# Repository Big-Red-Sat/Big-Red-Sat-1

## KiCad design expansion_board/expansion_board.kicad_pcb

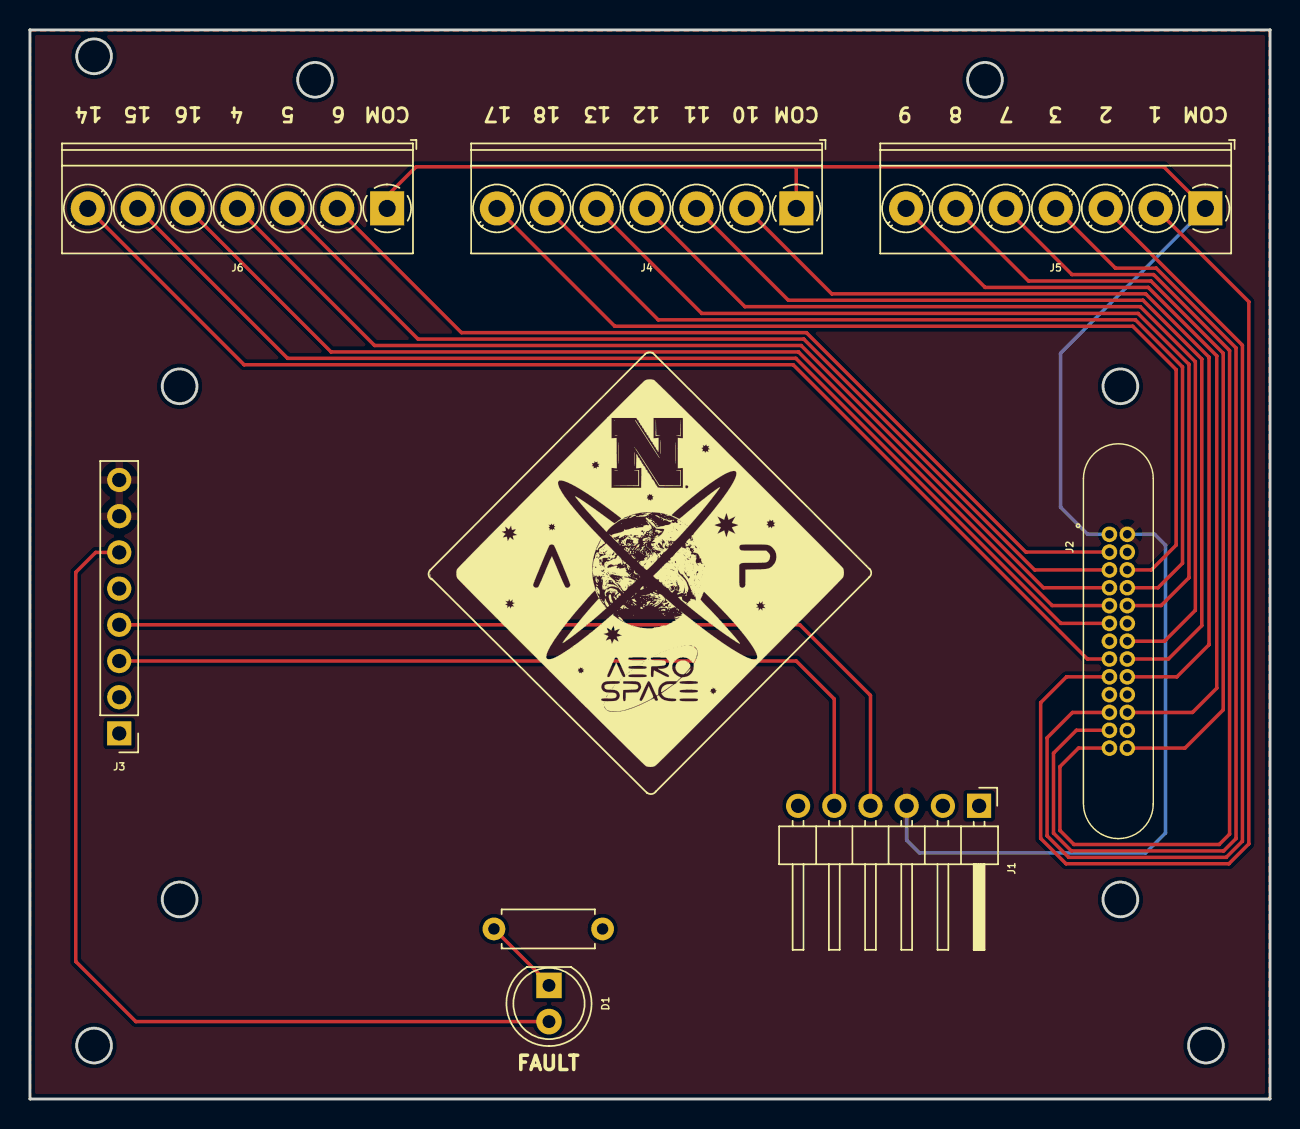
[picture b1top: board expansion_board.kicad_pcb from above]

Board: 2 copper layers, 87.0 x 75.0 mm, 8 parts (0 on the bottom side), 25 nets.

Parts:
D1: LED; LED_D5.0mm
FAULT: R; R_Axial_DIN0207_L6.3mm_D2.5mm_P7.62mm_Horizontal
J1: Conn_01x06_Female; PinHeader_1x06_P2.54mm_Horizontal
J2: G125-MH12605M4R; G125-MV12605M1P
J3: Conn_01x08_Female; PinHeader_1x08_P2.54mm_Vertical
J4, J5, J6: Screw_Terminal_01x07; TerminalBlock_Phoenix_PT-1,5-7-3.5-H_1x07_P3.50mm_Horizontal

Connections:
+3V3: J1.3, J2.14, J3.7, J3.8
GND: FAULT.2, J1.1, J2.19, J3.1, J3.2
unnamed: D1.1, FAULT.1
unnamed: D1.2, J3.6
unnamed: J1.4, J3.4
unnamed: J1.5, J3.3
unnamed: J2.1, J4.1, J5.1, J6.1
unnamed: J2.2, J6.2
unnamed: J2.3, J6.3
unnamed: J2.4, J6.4
unnamed: J2.5, J6.5
unnamed: J2.6, J6.6
unnamed: J2.8, J6.7
unnamed: J2.9, J5.2
unnamed: J2.11, J5.3
unnamed: J2.12, J5.4
unnamed: J2.13, J5.5
unnamed: J2.16, J4.7
unnamed: J2.17, J4.6
unnamed: J2.18, J4.5
unnamed: J2.20, J4.4
unnamed: J2.21, J4.3
unnamed: J2.22, J4.2
unnamed: J2.24, J5.7
unnamed: J2.26, J5.6

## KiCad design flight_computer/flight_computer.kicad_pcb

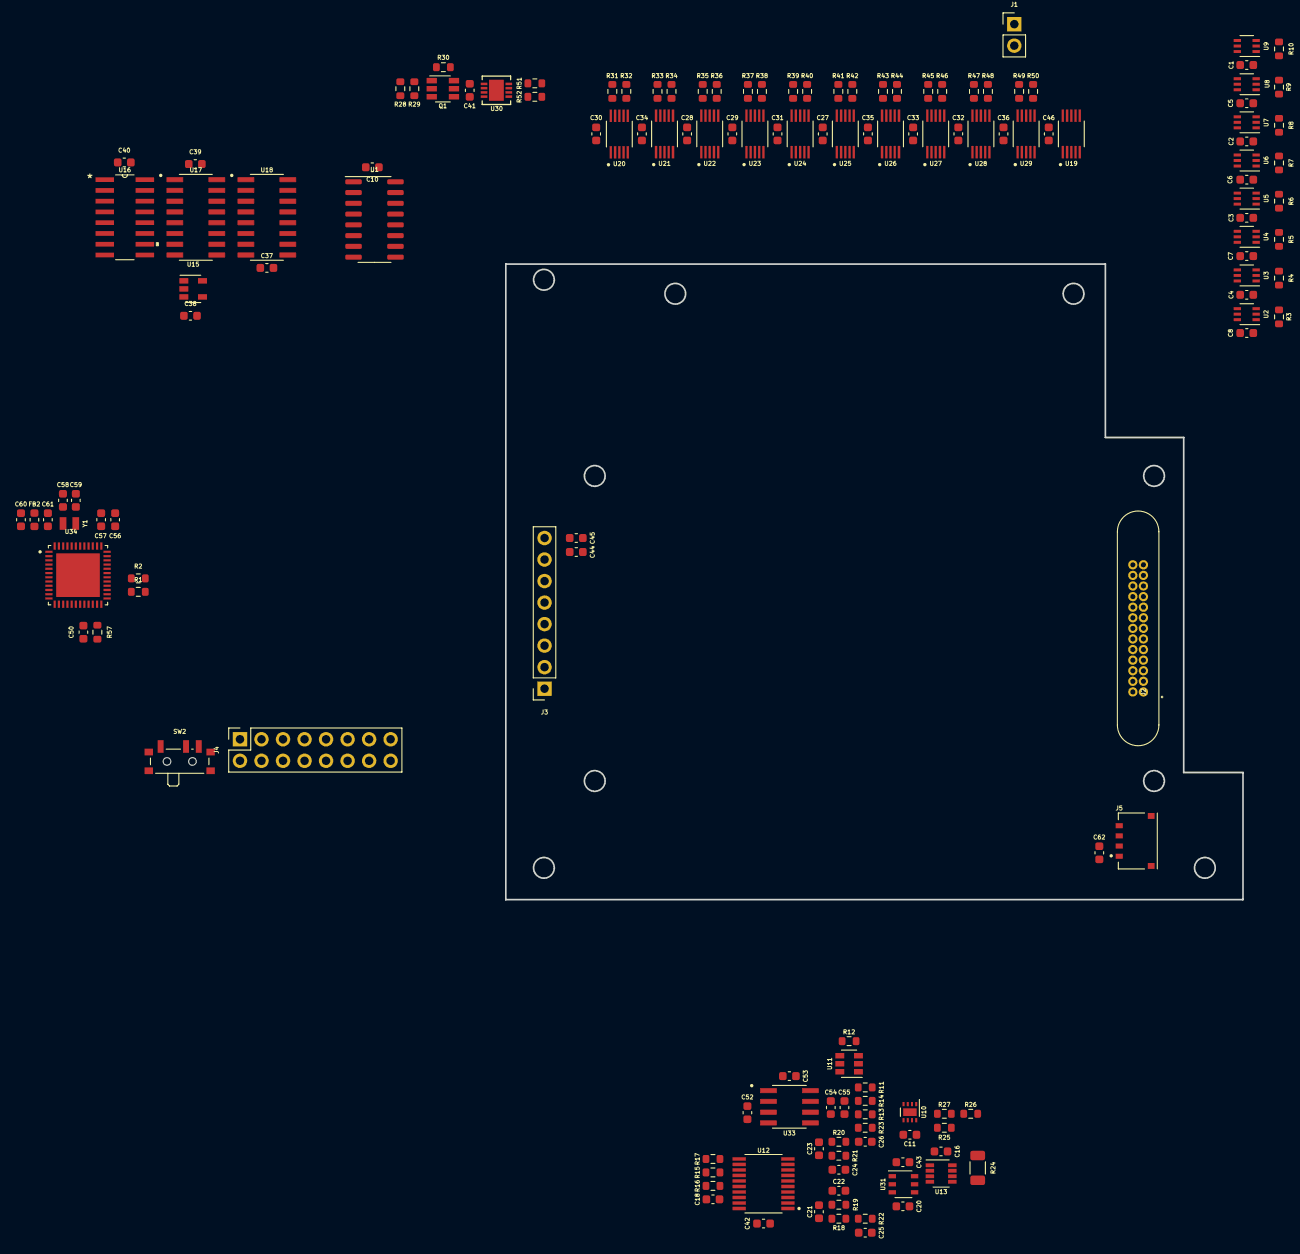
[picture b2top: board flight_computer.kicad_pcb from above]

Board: 4 copper layers, 145 parts (0 on the bottom side), 127 nets, no tracks yet.

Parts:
C1, C2, C3, C4, C5, C6, C7, C8, C10, C11, C16, C27, C28, C29, C30, C31, C32, C33, C34, C35, C36, C37, C38, C39, C40, C41, C42, C45, C46, C50, C53, C54, C56, C60, C61, C62: 0.1u; C_0603_1608Metric
C18: 220n; C_0603_1608Metric
C20, C43, C57: 1u; C_0603_1608Metric
C21, C22, C23, C24: 10n; C_0603_1608Metric
C25, C26, C44, C52: 10u; C_0603_1608Metric
C55: CP; C_0603_1608Metric
C58, C59: 10p; C_0603_1608Metric
FB2: Ferrite_Bead_Small; L_0603_1608Metric
J1: Silicon Cell; PinHeader_1x02_P2.54mm_Vertical
J2: G125-MV12605M1P
J3: Conn_01x08_Female; PinSocket_1x08_P2.54mm_Vertical
J4: Conn_02x07_Odd_Even; PinSocket_2x08_P2.54mm_Vertical
J5: 0781710004; MOLEX_0781710004
Q1: DMC2053UVT; TSOT-23-6
R1, R2: 4.7k; R_0603_1608Metric
R3: 50; R_0603_1608Metric
R4: 250; R_0603_1608Metric
R5: 500; R_0603_1608Metric
R6: 1000; R_0603_1608Metric
R7: 2000; R_0603_1608Metric
R8: 4000; R_0603_1608Metric
R9: 8000; R_0603_1608Metric
R10: 16000; R_0603_1608Metric
R11, R14: 100k; R_0603_1608Metric
R12, R28: 1k; R_0603_1608Metric
R13: 500k; R_0603_1608Metric
R15, R16, R17, R22, R23, R29, R30: 10k; R_0603_1608Metric
R18, R19, R20, R21, R25: 470; R_0603_1608Metric
R24: 510m; R_1206_3216Metric
R26, R27: 10M; R_0603_1608Metric
R31, R32, R33, R34, R35, R36, R37, R38, R39, R40, R41, R42, R43, R44, R45, R46, R47, R48, R49, R50, R57: R; R_0603_1608Metric
R51: 20k; R_0603_1608Metric
R52: 1; R_0603_1608Metric
SW2: SW_SPDT; SW_SPDT_PCM12
U1: 74HC590; SOIC-16_3.9x9.9mm_P1.27mm
U2, U3, U4, U5, U6, U7, U8, U9: ADG841YKSZ-500RL7
U10: OPA2387; WSON-8-1EP_2x2mm_P0.5mm_EP0.9x1.6mm
U11: MCP4725xxx-xCH; SOT-23-6
U12: ADS131M04IPWR; SOP65P640X120-20N
U13: INA190A4IDDFR
U15: SN74LVC1G14DRL; SOT-23-5
U16: CD4518BM96
U17, U18: CD4028BMT; SOIC127P600X175-16N
U19, U20, U21, U22, U23, U24, U25, U26, U27, U28, U29: MAX4736EUBT; SOP50P490X110-10N
U30: LT3092EDD#TRPBF; DFN-8_DD
U31: LT6654AMPS6-1.25; LT6654AMPS6-1.25-TRMPBF
U33: ICL7660CSAT; SOIC127P600X175-8N
U34: MSP430FR5969IRGZR; QFN50P700X700X100-49N
Y1: CM8V-T1A; XTAL_CM8V-T1A-32.768KHZ-7PF-20PPM-TA-QC

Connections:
+3V3: C1.1, C2.1, C3.1, C4.1, C5.1, C6.1, C7.1, C8.1, C10.1, C11.1, C16.1, C20.1, C27.1, C28.1, C29.1, C30.1, C31.1, C32.1, C33.1, C34.1, C35.1, C36.1, C37.1, C38.1, C39.1, C40.1, C42.1, C44.1, C45.2, C46.1, C53.2, C56.1, C57.1, C61.1, C62.2, FB2.1, J3.7, J3.8, J5.2, Q1.2, R1.2, R2.2, R15.1, R16.1, R17.1, R30.1, R57.2, SW2.2, U1.16, U2.6, U3.6, U4.6, U5.6, U6.6, U7.6, U8.6, U9.6, U10.8, U11.3, U12.1, U12.20, U13.1, U13.2, U15.5, U16.16, U17.16, U18.16, U19.8, U20.8, U21.8, U22.8, U23.8, U24.8, U25.8, U26.8, U27.8, U28.8, U29.8, U31.4, U33.8, U34.37
-3V3: C54.2, C55.2, R13.2, U10.4, U10.9, U33.5
/Curve Tracer/ADC_CLK: U12.17, U34.18
/Curve Tracer/ADC_CS: R15.2, U12.12, U34.17
/Curve Tracer/ADC_DRDY: R16.2, U12.13, U34.4
/Curve Tracer/ADC_SYNC: R17.2, U12.11, U34.40
/Curve Tracer/LADDER_VOLTAGE: R10.1, R24.1, R26.2, U9.2, U10.1, U10.2, U13.8
/Curve Tracer/MISO: U12.15, U34.32
/Curve Tracer/MOSI: U12.16, U34.31
/Curve Tracer/SCLK: U12.14, U34.26
/Payload Controller/0-9_CLOCK: U16.1, U34.35
/Payload Controller/10-19_CLOCK: U16.9, U34.34
/Payload Controller/ENABLE_PANEL_SWITCH: U15.2, U16.10, U34.24
/Payload Controller/ENABLE_TEST_SOURCE: R28.2, U34.16
/Payload Controller/LADDER_CLOCK: U1.11, U34.9
/Payload Controller/LADDER_LATCH: U1.13, U34.11
/Payload Controller/RESET_PANEL_SWITCH: U16.7, U16.15, U34.25
/Payload Controller/REVERSE_BIAS: U19.1, U19.5, U34.39
/Payload Controller/SCL: J5.3, R1.1, U11.5, U34.28
/Payload Controller/SDA: J5.4, R2.1, U11.4, U34.29
/Payload Controller/~LADDER_EN: U1.12, U34.3
/Payload Controller/~LADDER_RESET: U1.10, U34.10
/Perovskite Switches/PANEL_POSITIVE: R24.2, U13.7, U19.4, U19.9
FAULT: J3.5, U34.30
GND: C1.2, C2.2, C3.2, C4.2, C5.2, C6.2, C7.2, C8.2, C10.2, C11.2, C16.2, C18.2, C20.2, C22.2, C24.2, C25.2, C26.2, C27.2, C28.2, C29.2, C30.2, C31.2, C32.2, C33.2, C34.2, C35.2, C36.2, C37.2, C38.2, C39.2, C40.2, C41.1, C42.2, C43.2, C44.2, C45.1, C46.2, C50.1, C53.1, C54.1, C55.1, C56.2, C57.2, C58.1, C59.1, C60.2, C61.2, C62.1, J3.1, J3.2, J4.9, J5.1, J5.S1, J5.S2, Q1.5, R3.2, R12.1, R14.2, R19.2, R21.2, R27.1, R29.2, R31.1, R32.1, R33.1, R34.1, R35.1, R36.1, R37.1, R38.1, R39.1, R40.1, R41.1, R42.1, R43.1, R44.1, R45.1, R46.1, R47.1, R48.1, R49.1, R50.1, U1.8, U1.14, U2.1, U2.3, U3.3, U4.3, U5.3, U6.3, U7.3, U8.3, U9.3, U11.2, U12.2, U12.19, U13.4, U15.3, U16.8, U17.8, U18.8, U19.2, U19.3, U19.7, U20.3, U21.3, U22.3, U23.3, U24.3, U25.3, U26.3, U27.3, U28.3, U29.3, U31.1, U31.2, U33.3, U33.6, U34.36, U34.41, U34.44, U34.47, U34.49
unnamed: C18.1, U12.18
unnamed: C21.1, R18.1, U12.3
unnamed: C21.2, C22.1, R19.1, U12.4
unnamed: C23.1, R20.1, U12.10
unnamed: C23.2, C24.1, R21.1, U12.9
unnamed: C25.1, R18.2, R22.1
unnamed: C26.1, R20.2, R23.1
unnamed: C41.2, Q1.4, U30.7, U30.8
unnamed: C43.1, U13.3, U31.6
unnamed: C52.1, U33.2
unnamed: C52.2, U33.4
unnamed: C58.2, U34.46, Y1.1
unnamed: C59.2, U34.43, Y1.2
unnamed: C60.1, FB2.2, U34.48
unnamed: J1.2, U29.10
unnamed: J4.2, SW2.1
unnamed: J4.4, SW2.3
unnamed: Q1.1, R28.1, R29.1
unnamed: Q1.3, Q1.6, R30.2
unnamed: R3.1, R4.2, U2.2, U3.1
unnamed: R4.1, R5.2, U3.2, U4.1
unnamed: R5.1, R6.2, U4.2, U5.1
unnamed: R6.1, R7.2, U5.2, U6.1
unnamed: R7.1, R8.2, U6.2, U7.1
unnamed: R8.1, R9.2, U7.2, U8.1
unnamed: R9.1, R10.2, U8.2, U9.1
unnamed: R11.1, U11.1
unnamed: R11.2, R13.1, R14.1, U10.3
unnamed: R12.2, U11.6
unnamed: R22.2, U13.5
unnamed: R23.2, U10.6, U10.7
unnamed: R25.1, U10.5
unnamed: R25.2, R26.1, R27.2
unnamed: R31.2, U20.9
unnamed: R32.2, U20.7
unnamed: R33.2, U21.9
unnamed: R34.2, U21.7
unnamed: R35.2, U22.9
unnamed: R36.2, U22.7
unnamed: R37.2, U23.9
unnamed: R38.2, U23.7
unnamed: R39.2, U24.9
unnamed: R40.2, U24.7
unnamed: R41.2, U25.9
unnamed: R42.2, U25.7
unnamed: R43.2, U26.9
unnamed: R44.2, U26.7
unnamed: R45.2, U27.9
unnamed: R46.2, U27.7
unnamed: R47.2, U28.9
unnamed: R48.2, U28.7
unnamed: R49.2, U29.9
unnamed: R50.2, U29.7
unnamed: R51.1, R52.1, U29.6
unnamed: R51.2, U30.4
unnamed: R52.2, U30.1, U30.2, U30.9
unnamed: U1.1, U3.4
unnamed: U1.2, U4.4
unnamed: U1.3, U5.4
unnamed: U1.4, U6.4
unnamed: U1.5, U7.4
unnamed: U1.6, U8.4
unnamed: U1.7, U9.4
unnamed: U1.15, U2.4
unnamed: U15.4, U16.2
unnamed: U16.3, U17.10
unnamed: U16.4, U17.13
unnamed: U16.5, U17.12
unnamed: U16.6, U17.11
unnamed: U16.11, U18.10
unnamed: U16.12, U18.13
unnamed: U16.13, U18.12
unnamed: U16.14, U18.11
unnamed: U17.1, U22.5
unnamed: U17.2, U21.5
unnamed: U17.3, U20.5
unnamed: U17.4, U23.1
unnamed: U17.5, U24.1
unnamed: U17.6, U22.1
unnamed: U17.7, U23.5
unnamed: U17.9, U24.5
unnamed: U17.14, U20.1
unnamed: U17.15, U21.1
unnamed: U18.1, U27.5
unnamed: U18.2, U26.5
unnamed: U18.3, U25.5
unnamed: U18.4, U28.1
unnamed: U18.5, U29.1
unnamed: U18.6, U27.1
unnamed: U18.7, U28.5
unnamed: U18.9, U29.5
unnamed: U18.14, U25.1
unnamed: U18.15, U26.1
unnamed: U19.6, U20.2, U20.4, U21.2, U21.4, U22.2, U22.4, U23.2, U23.4, U24.2, U24.4, U25.2, U25.4, U26.2, U26.4, U27.2, U27.4, U28.2, U28.4, U29.2, U29.4
PAYLOAD_RST: C50.2, J3.6, R57.1, U34.23
RX_IN: J3.4, U34.21
TCK: J4.7, U34.15
TDI: J4.3, U34.13
TDO: J4.1, U34.12
TEST: J4.8, U34.22
TMS: J4.5, U34.14
TX_OUT: J3.3, U34.20

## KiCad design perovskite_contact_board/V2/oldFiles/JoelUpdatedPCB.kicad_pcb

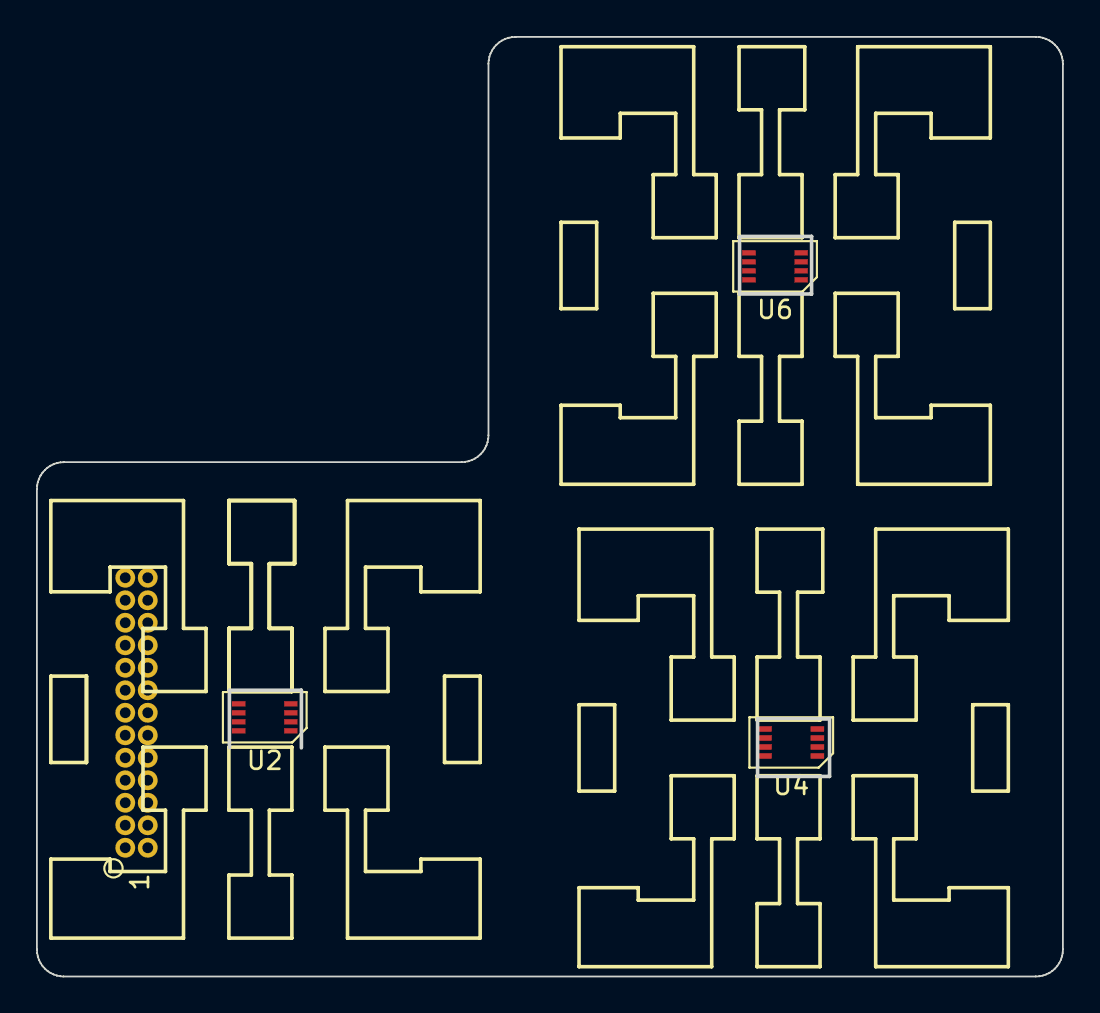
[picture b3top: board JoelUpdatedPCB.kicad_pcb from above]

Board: 2 copper layers, 57.0 x 52.2 mm, 4 parts (0 on the bottom side), 4 nets, no tracks yet.

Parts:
J18: G125-MV12605M1R; BOTTOM-G125-MV12605M1R
U2, U4, U6: MCP9804

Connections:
GND: J18.26, U2.4 (GND), U2.5 (A2), U2.6 (A1), U4.4 (GND), U4.5 (A2), U4.7 (A0), U6.4 (GND), U6.6 (A1), U6.7 (A0)
SCL: J18.24, U2.2 (SCL), U4.2 (SCL), U6.2 (SCL)
SDA: J18.23, U2.1 (SDA), U4.1 (SDA), U6.1 (SDA)
VCC: J18.25, U2.7 (A0), U2.8 (VDD), U4.6 (A1), U4.8 (VDD), U6.5 (A2), U6.8 (VDD)

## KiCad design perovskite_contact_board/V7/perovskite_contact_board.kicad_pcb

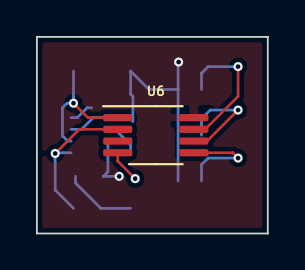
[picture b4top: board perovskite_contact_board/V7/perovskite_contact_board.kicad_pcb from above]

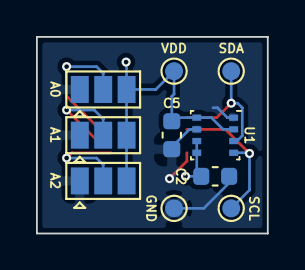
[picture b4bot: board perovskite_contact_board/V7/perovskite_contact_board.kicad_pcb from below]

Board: 2 copper layers, 12.8 x 10.9 mm, 11 parts (10 on the bottom side), 7 nets.

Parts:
A0, A1, A2: Jumper_3_Open; SolderJumper-3_P1.3mm_Open_Pad1.0x1.5mm
C2, C5: 0.1u; C_0603_1608Metric
JP103.1, JP103.10, JP103.11, JP103.12: Conn_01x01; TestPoint_Pad_D1.0mm
U1: BME280; Bosch_LGA-8_2.5x2.5mm_P0.65mm_ClockwisePinNumbering
U6: MCP9808_MSOP; MSOP-8_3x3mm_P0.65mm

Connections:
GND: A0.1, A1.1, A2.1, C2.2, C5.2, JP103.1.1, U1.1, U1.7, U6.4
unnamed: A2.2, U6.5
unnamed: A1.2, U6.6
unnamed: A0.2, U6.7
SCL: JP103.11.1, U1.4, U6.2
SDA: JP103.12.1, U1.3, U6.1
VDDF: A0.3, A1.3, A2.3, C2.1, C5.1, JP103.10.1, U1.2, U1.5, U1.6, U1.8, U6.8

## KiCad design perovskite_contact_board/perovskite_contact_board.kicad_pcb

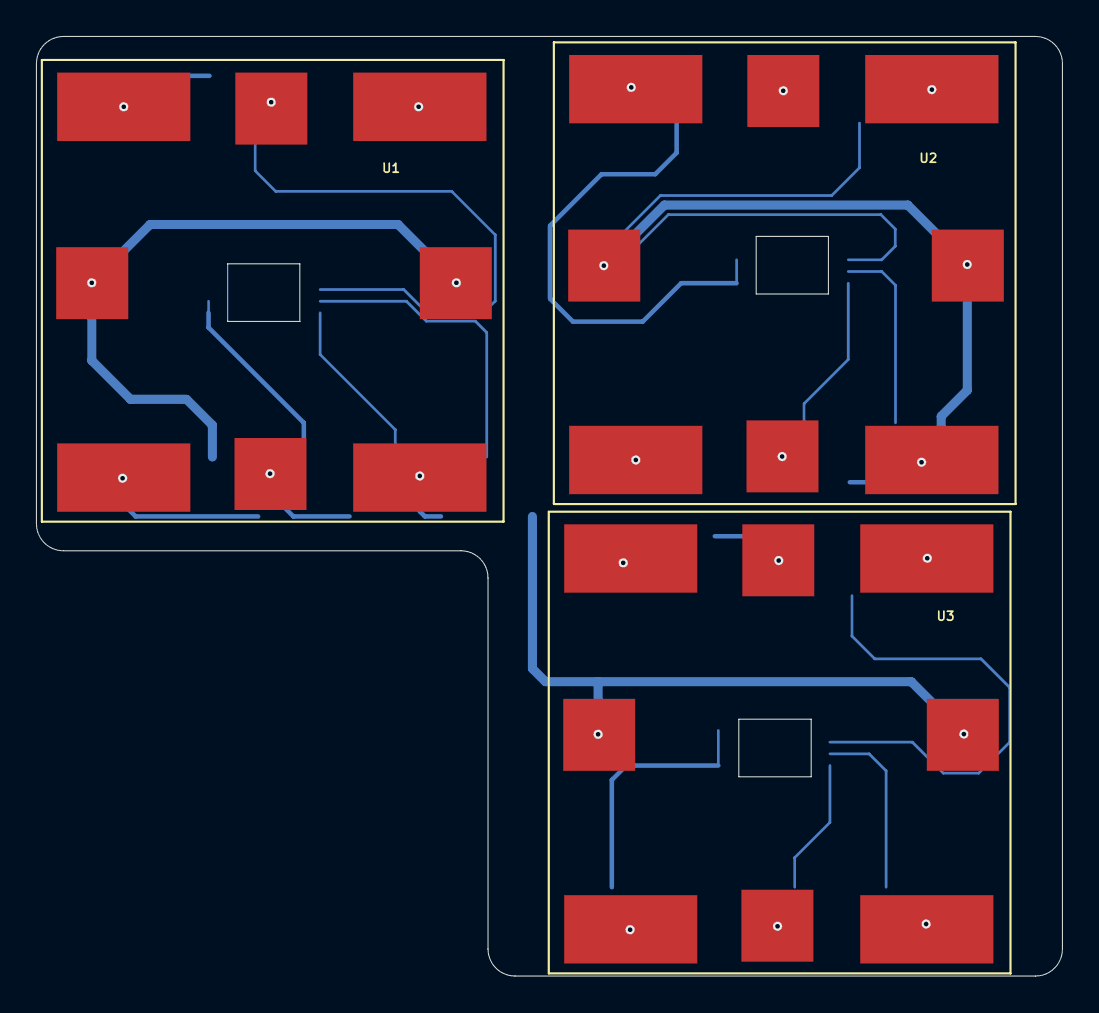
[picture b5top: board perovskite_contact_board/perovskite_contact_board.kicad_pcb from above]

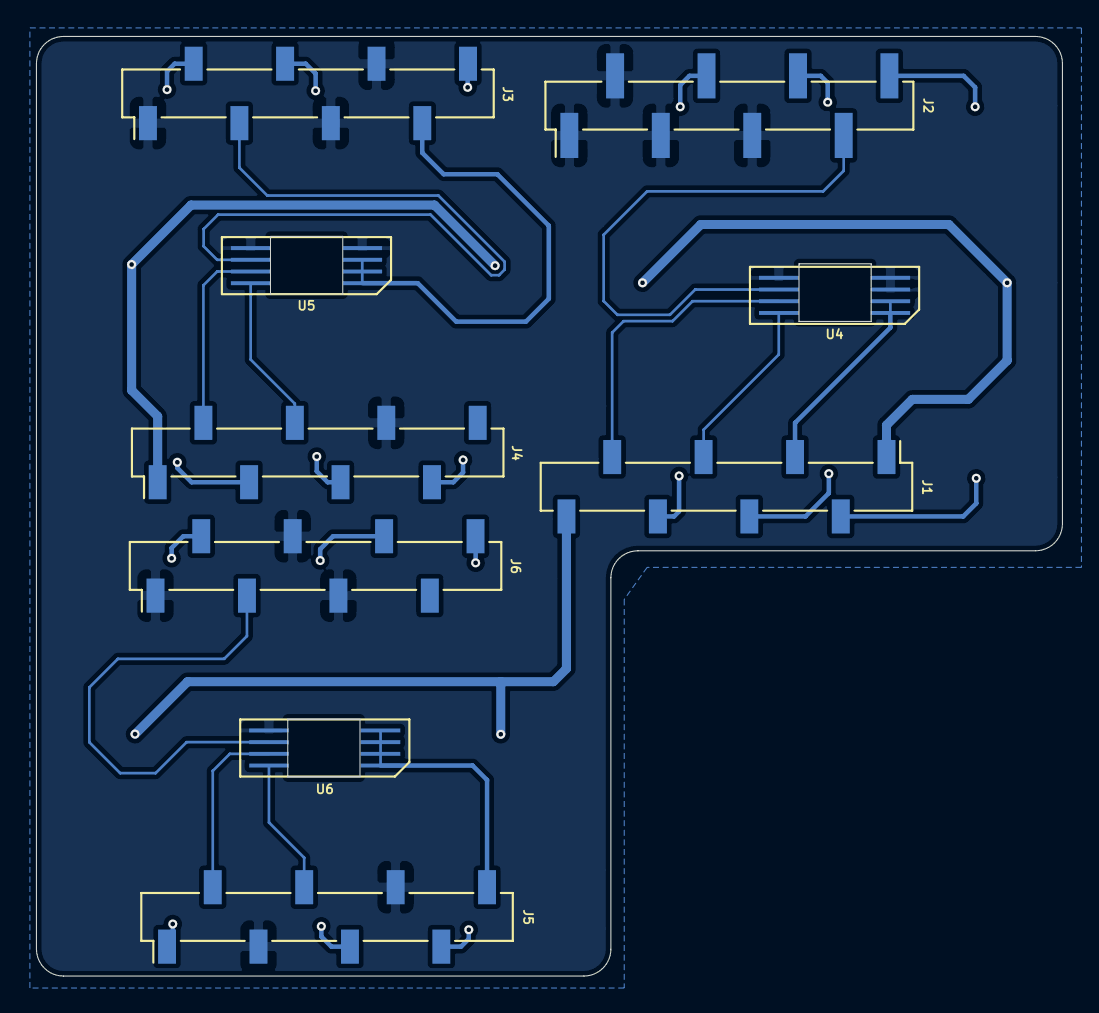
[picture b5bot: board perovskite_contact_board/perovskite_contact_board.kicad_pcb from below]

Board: 2 copper layers, 57.0 x 52.2 mm, 12 parts (9 on the bottom side), 34 nets.

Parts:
J1, J3, J4, J5, J6: Conn_01x08; PinSocket_1x08_P2.54mm_Vertical_SMD_Pin1Left
J2: Conn_01x08; PinHeader_1x08_P2.54mm_Vertical_SMD_Pin1Left
U1, U2, U3: Perovskite_CP_6_Cell; Perovskite
U4, U5, U6: MCP9808_MSOP; MCP9804_With_Hole

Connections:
ALERT1: J2.7, U4.3
ALERT2: J3.3, U5.3
ALERT3: J6.3, U6.3
CELL_1: J2.8, U1.1
CELL_2: J2.6, U1.2
CELL_3: J2.4, U1.3
CELL_4: J1.6, U1.4
CELL_5: J1.4, U1.5
CELL_6: J1.2, U1.6
CELL_7: J3.8, U2.1
CELL_8: J3.4, U2.2
CELL_9: J3.2, U2.3
CELL_10: J4.3, U2.4
CELL_11: J4.5, U2.5
CELL_12: J4.7, U2.6
CELL_13: J6.8, U3.1
CELL_14: J6.6, U3.2
CELL_15: J6.2, U3.3
CELL_16: J5.1, U3.4
CELL_17: J5.5, U3.5
CELL_18: J5.7, U3.6
CP: J1.1, U1.7
CP_2: J4.1, U2.7
CP_3: J1.8, U3.7
GND: J2.1, J2.2, J2.3, J2.5, J3.1, J3.5, J3.6, J4.6, J5.3, J5.6, J6.1, J6.4, J6.5, U4.4, U4.5, U4.6, U5.4, U5.5, U6.4
unnamed: J1.3, U4.7, U4.8
unnamed: J3.7, U5.6, U5.7, U5.8
unnamed: J5.8, U6.5, U6.6, U6.7, U6.8
SCL: J1.7, U4.2
SCL_2: J4.2, U5.2
SCL_3: J5.2, U6.2
SDA: J1.5, U4.1
SDA_2: J4.4, U5.1
SDA_3: J5.4, U6.1

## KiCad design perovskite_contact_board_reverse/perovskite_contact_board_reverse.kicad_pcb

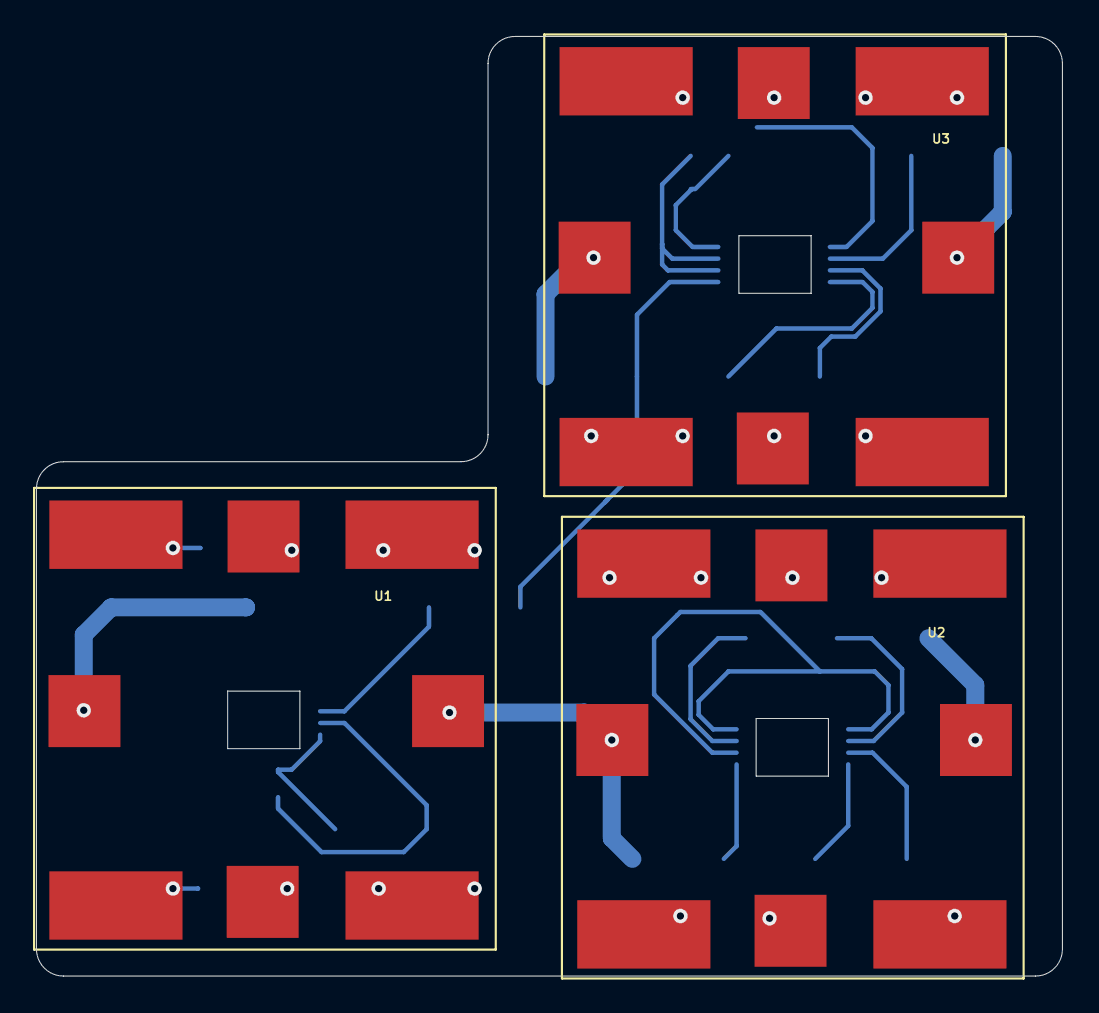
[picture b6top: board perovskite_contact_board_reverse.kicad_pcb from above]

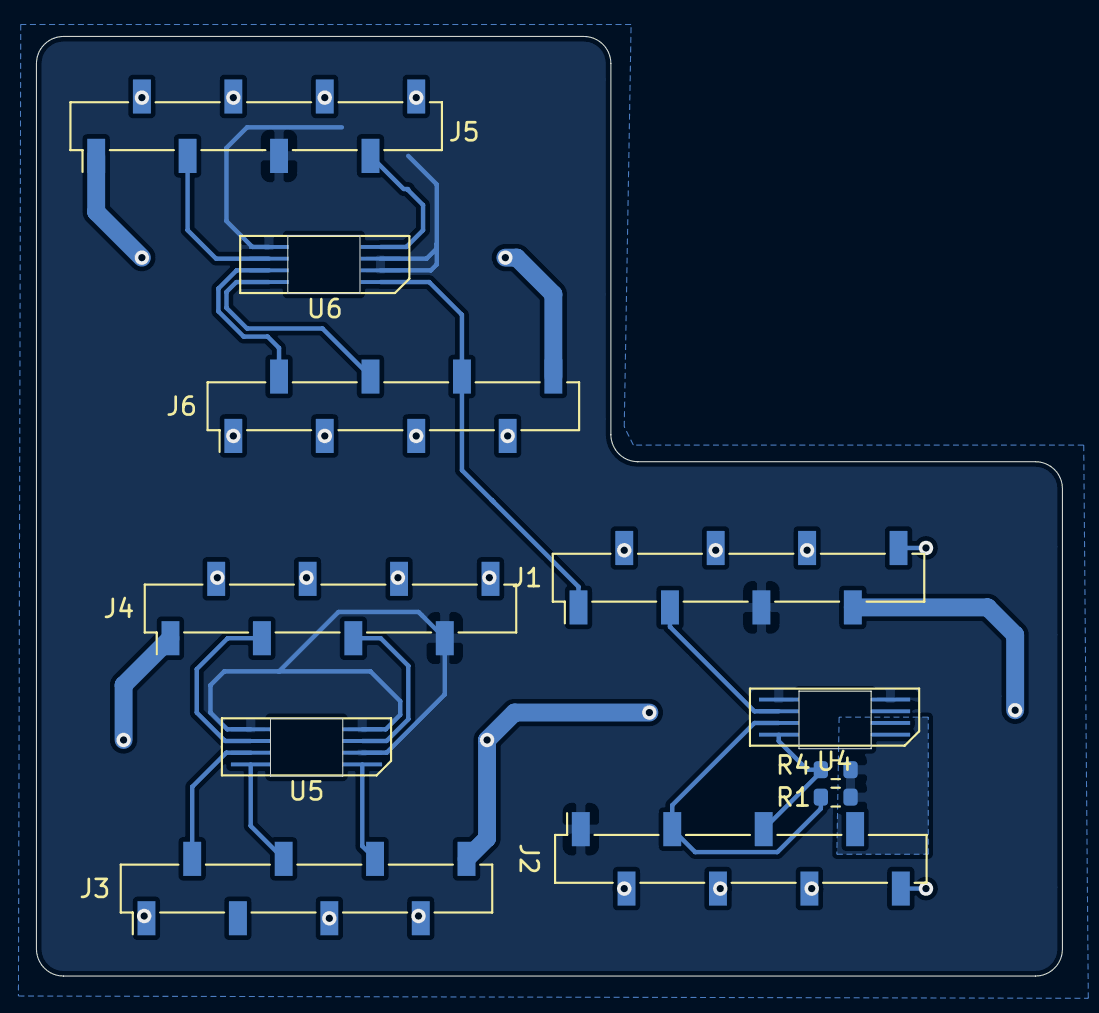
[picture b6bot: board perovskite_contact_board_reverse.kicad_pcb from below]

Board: 2 copper layers, 57.0 x 52.2 mm, 14 parts (11 on the bottom side), 27 nets.

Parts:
J1, J3, J4, J5, J6: Conn_01x08; PinSocket_1x08_P2.54mm_Vertical_SMD_Pin1Left
J2: Conn_01x08; PinSocket_1x08_P2.54mm_Vertical_SMD_Pin1Right
R1, R4: R; R_0603_1608Metric
U1, U2, U3: Perovskite_CP_6_Cell; Perovskite
U4, U5, U6: MCP9808_MSOP; MCP9804_With_Hole

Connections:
+5V: R1.2, R4.1
ALERT1: J1.3, U4.3
ALERT2: J4.3, U5.3
ALERT3: J5.3, U6.3
CELL_1: J1.8, U1.1
CELL_2: J1.6, U1.2
CELL_3: J1.2, J1.4, U1.3
CELL_4: J2.2, J2.4, U1.4
CELL_5: J2.6, U1.5
CELL_6: J2.8, U1.6
CELL_7: J4.6, J4.8, U2.1
CELL_8: J4.4, U2.2
CELL_9: J4.2, U2.3
CELL_10: J3.1, U2.4
CELL_11: J3.5, U2.5
CELL_12: J3.7, U2.6
CELL_13: J5.8, U3.1
CELL_14: J5.6, U3.2
CELL_15: J5.2, J5.4, U3.3
CELL_16: J6.1, U3.4
CELL_17: J6.3, U3.5
CELL_18: J6.5, J6.7, U3.6
CP: J1.7, J3.8, J4.1, J5.1, J6.8, U1.7, U2.7, U3.7
GND: J1.5, J2.1, J4.7, J5.5, U4.4, U4.5, U4.6, U5.4, U5.5, U5.7, U6.4, U6.6, U6.7
SCL: J2.3, J3.2, J6.2, R1.1, U4.2, U5.2, U6.2
SDA: J2.5, J3.4, J6.4, R4.2, U4.1, U5.1, U6.1
VDD: J1.1, J2.7, J3.6, J4.5, J5.7, J6.6, U4.7, U4.8, U5.6, U5.8, U6.5, U6.8

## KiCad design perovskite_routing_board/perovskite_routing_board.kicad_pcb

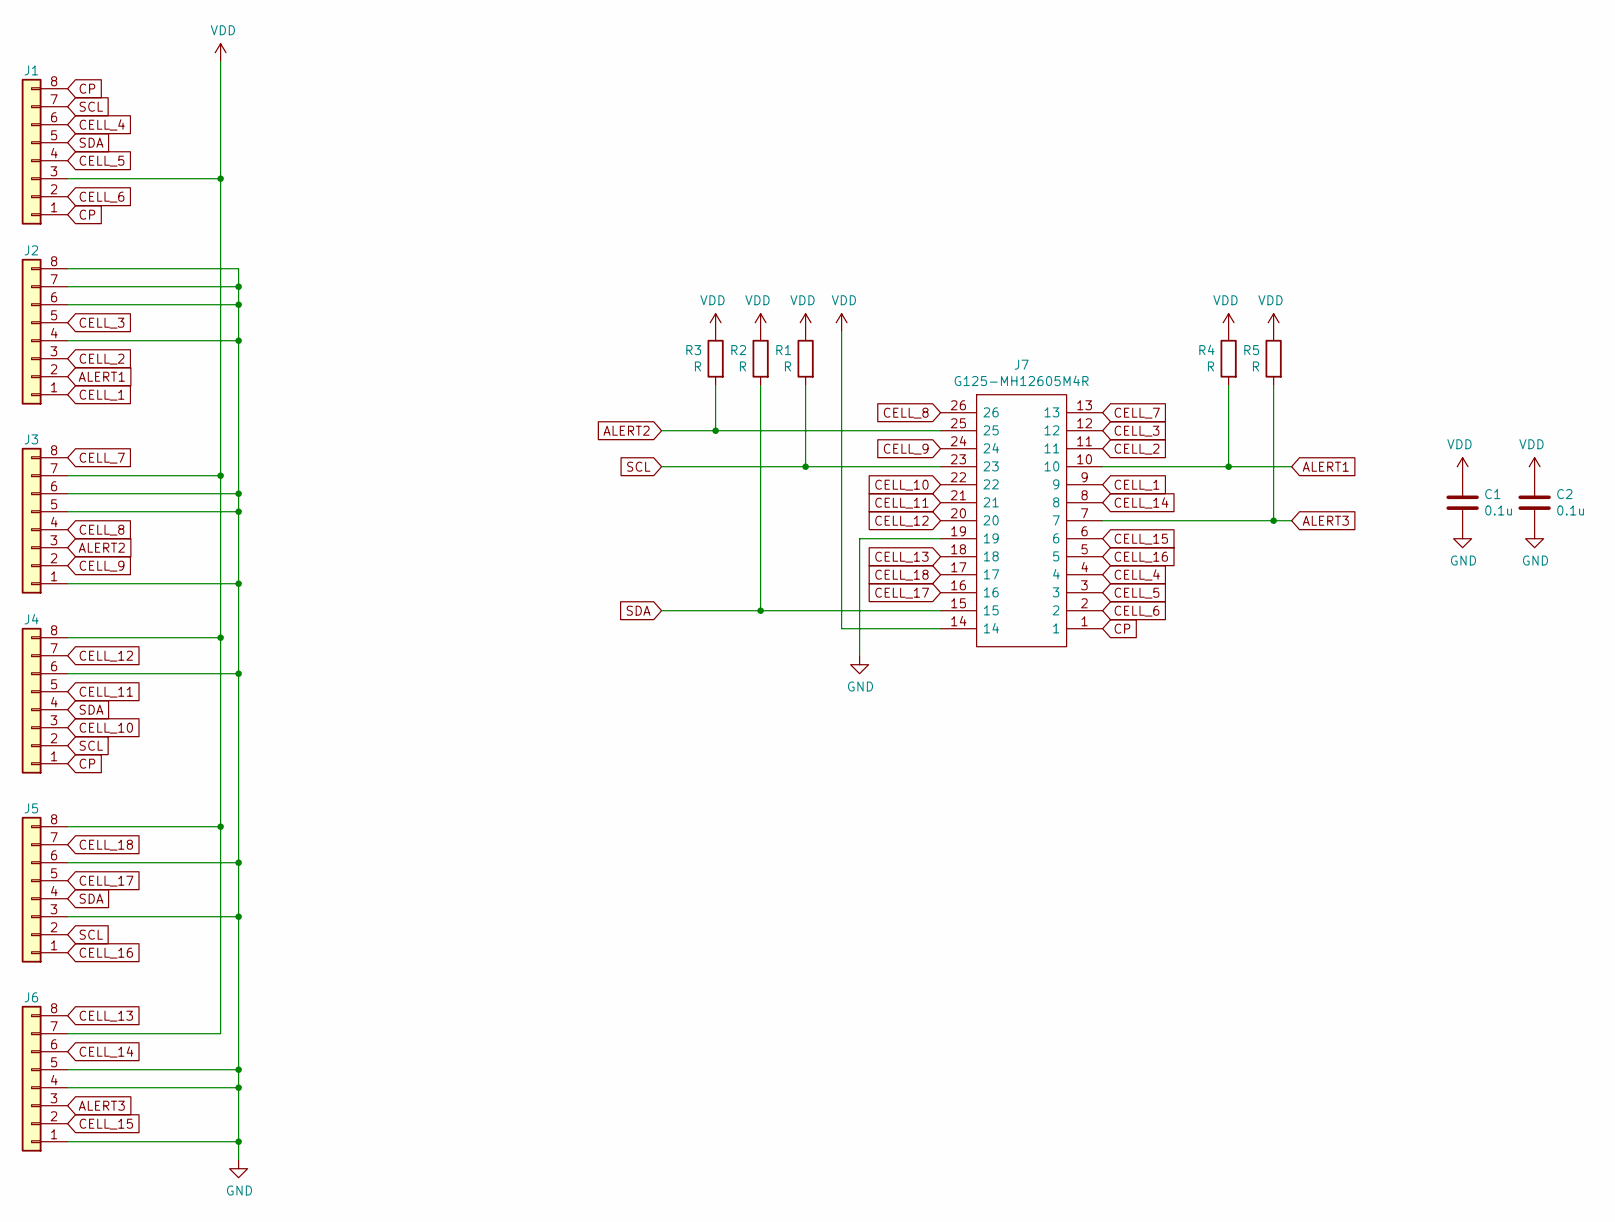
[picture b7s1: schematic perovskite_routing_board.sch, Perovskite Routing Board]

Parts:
C1, C2: 0.1u; C_0603_1608Metric
J1, J2, J3, J4, J5, J6: Conn_01x08; PinHeader_1x08_P2.54mm_Vertical
J7: G125-MH12605M4R; G125-MV12605M1P; Manufacturer_Part_Number G125-MH12605M4R; Mouser Part Number 855-G125MH1265M4RM4R
R1, R2, R3, R4, R5: R; R_0603_1608Metric

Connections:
ALERT1: J2.2, J7.10, R4.2
ALERT2: J3.3, J7.25, R3.2
ALERT3: J6.3, J7.7, R5.2
CELL_1: J2.1, J7.9
CELL_2: J2.3, J7.11
CELL_3: J2.5, J7.12
CELL_4: J1.6, J7.4
CELL_5: J1.4, J7.3
CELL_6: J1.2, J7.2
CELL_7: J3.8, J7.13
CELL_8: J3.4, J7.26
CELL_9: J3.2, J7.24
CELL_10: J4.3, J7.22
CELL_11: J4.5, J7.21
CELL_12: J4.7, J7.20
CELL_13: J6.8, J7.18
CELL_14: J6.6, J7.8
CELL_15: J6.2, J7.6
CELL_16: J5.1, J7.5
CELL_17: J5.5, J7.16
CELL_18: J5.7, J7.17
CP: J1.1, J1.8, J4.1, J7.1
GND: C1.2, C2.2, J2.4, J2.6, J2.7, J2.8, J3.1, J3.5, J3.6, J4.6, J5.3, J5.6, J6.1, J6.4, J6.5, J7.19
SCL: J1.7, J4.2, J5.2, J7.23, R1.2
SDA: J1.5, J4.4, J5.4, J7.15, R2.2
VDD: C1.1, C2.1, J1.3, J3.7, J4.8, J5.8, J6.7, J7.14, R1.1, R2.1, R3.1, R4.1, R5.1

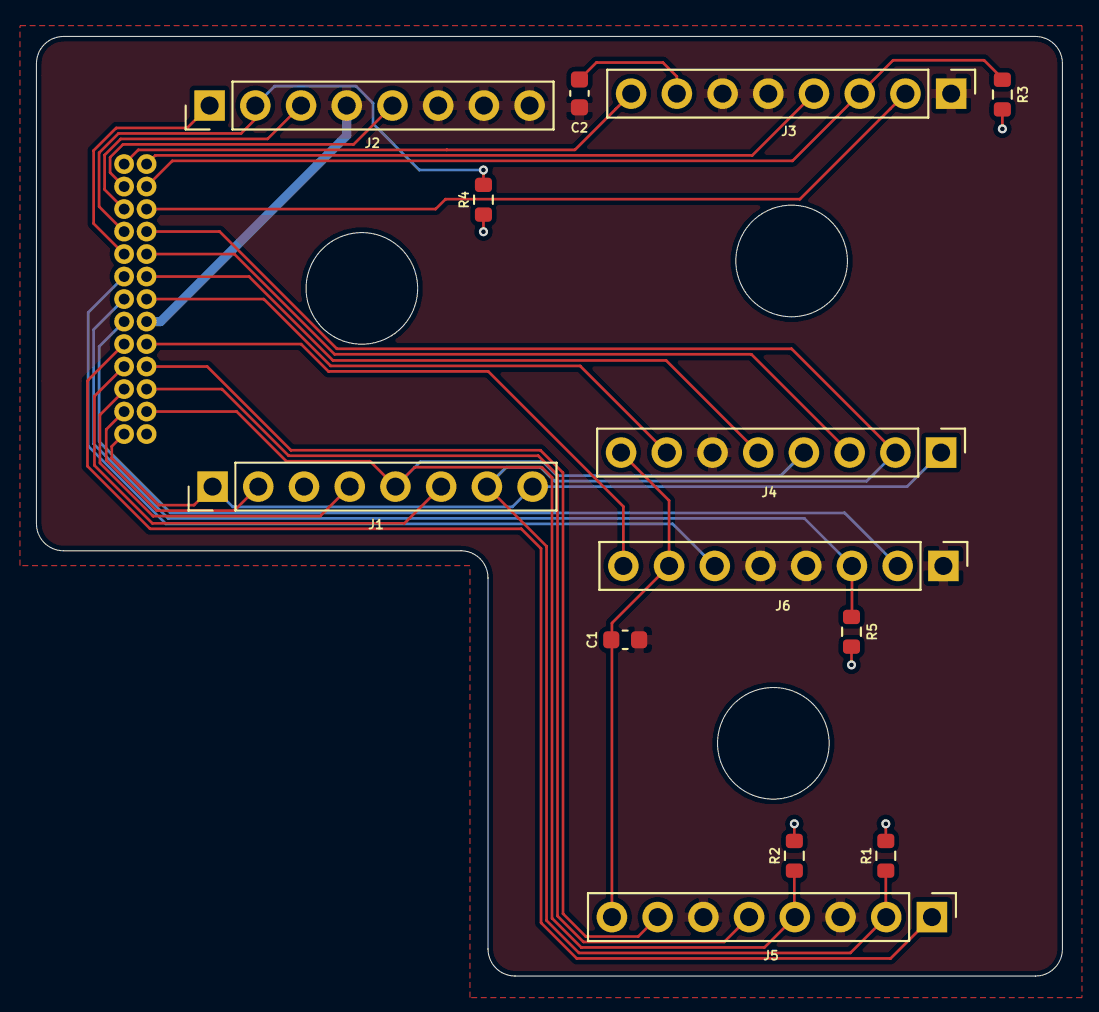
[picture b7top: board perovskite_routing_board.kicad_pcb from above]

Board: 2 copper layers, 57.0 x 52.2 mm, 14 parts (1 on the bottom side), 26 nets.

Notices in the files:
perovskite_contact_board/V7/perovskite_contact_board.kicad_pcb:
Copyright (c) 2023
perovskite_contact_board/perovskite_contact_board.kicad_pcb:
Copyright (c) 2022
parts and their libraries:
Copyright 2021 Accelerated Designs. All rights reserved.
